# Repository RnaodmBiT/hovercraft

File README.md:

# MiniBot

This project will produce a PCB design that can be used for prototyping remote control vehicles. It is inspired by the University of Canterbury ECE Departments 'Wacky Racers' competition. The objective is to follow most of the rules of that competition however the entire design will fit on a single PCB and be as small as possible.

 ## Requirements
  - Support a number of external ESCs and Servos.
  - Be remote controlled. This might require a second USB dongle to be produced if Bluetooth or WiFi isn't used.
  - It should include an accelerometer, gyroscope, and magnetometer for any control systems.
  - Be programmable over SWD or USB.
  - Use as minimum number of parts.
  - Make use of an STM32 microcontroller.
  - Provide external PIO access for use in different projects.

 ## Connectivity
  - Radio
    - RN41
      - UART
      - LED connected to GPIO5 (Open Drain)
      - Connect GPIOs 3/4/6 to GND
      - Connect GPIO 7 to ground with solder bridge high

  - Accelerometer
    - LSM6DS3US
      - I2C

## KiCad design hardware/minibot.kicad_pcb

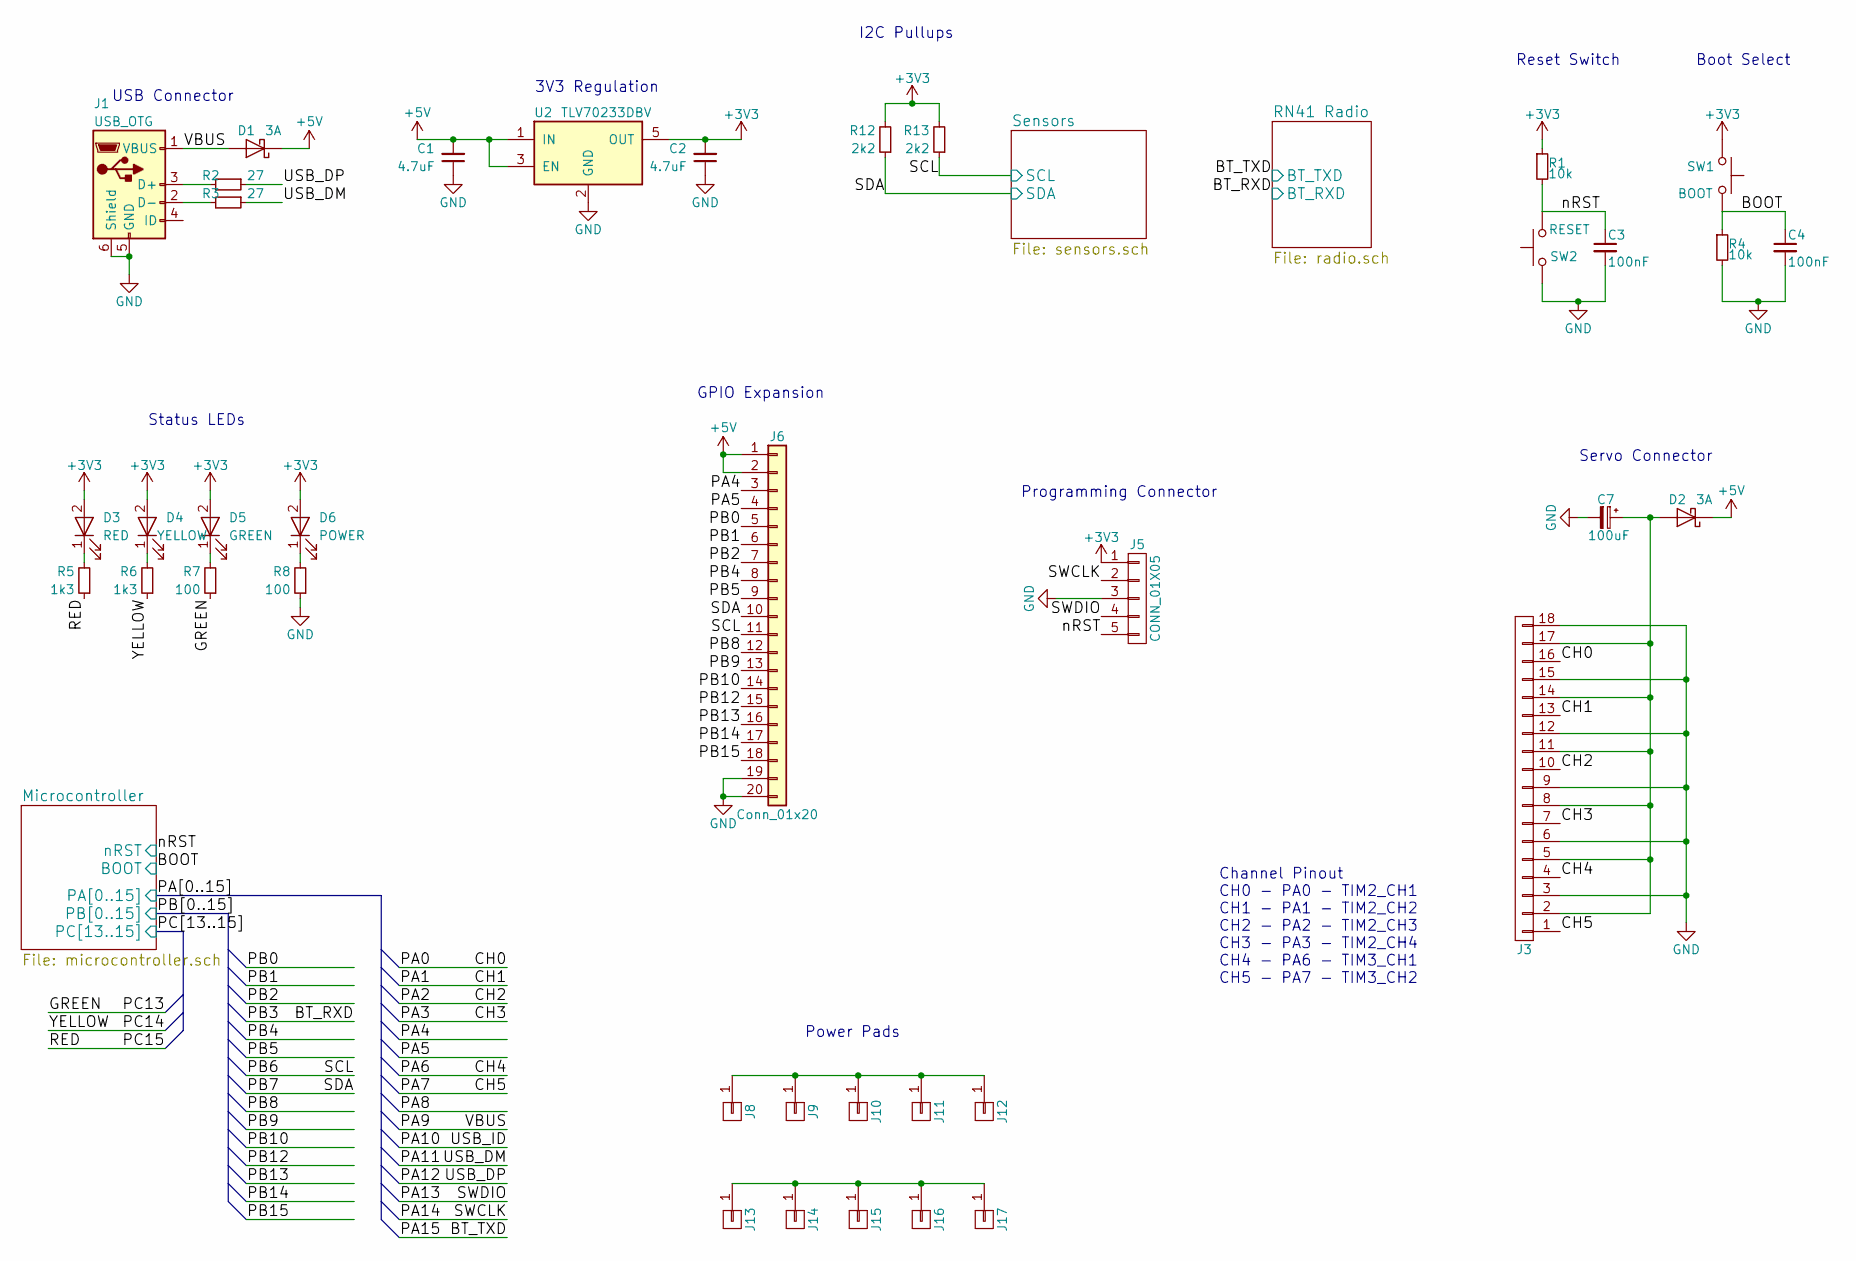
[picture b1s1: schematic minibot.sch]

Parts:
C1, C2: 4.7uF; C_0805
C3, C4: 100nF; C_0603
C7: 100uF; CP_Elec_6.3x5.3
D1, D2: 3A; D_SMA
D3: RED; LED_0603
D4: YELLOW; LED_0603
D5: GREEN; LED_0603
D6: POWER; LED_0603
J1: USB_OTG; USB_Micro-B
J3: CONN_01X18; Pin_Header_Angled_3x06_Pitch2.54mm
J5: CONN_01X05; Pin_Header_Straight_1x05_Pitch2.54mm
J6: Conn_01x20; IDC_Header_Straight_20pins
J8, J9, J10, J11, J12, J13, J14, J15, J16, J17: CONN_01X01; Pad
R1, R4: 10k; R_0603
R2, R3: 27; R_0603
R5, R6: 1k3; R_0603
R7, R8: 100; R_0603
R12, R13: 2k2; R_0603
SW1: BOOT; Panasonic_EVQPUK_EVQPUB
SW2: RESET; Panasonic_EVQPUK_EVQPUB
U2: TLV70233DBV; SOT-23-5

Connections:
+3V3: C2.2, D3.2 (A), D4.2 (A), D5.2 (A), D6.2 (A), J5.1, R1.1, R12.2, R13.2, SW1.1, U2.5 (OUT); also elsewhere on the board
+5V: C1.2, D1.1 (K), D2.1 (K), J6.1, J6.2, U2.1 (IN), U2.3 (EN)
/BOOT: C4.1, R4.1, SW1.2; also elsewhere on the board
/CH0: J3.16; also elsewhere on the board
/CH1: J3.13; also elsewhere on the board
/CH2: J3.10; also elsewhere on the board
/CH3: J3.7; also elsewhere on the board
/CH4: J3.4; also elsewhere on the board
/CH5: J3.1; also elsewhere on the board
/GREEN: R7.1; also elsewhere on the board
/PA4: J6.3; also elsewhere on the board
/PA5: J6.4; also elsewhere on the board
/PA9: D1.2 (A), J1.1 (VBUS); also elsewhere on the board
/PA11: R3.1; also elsewhere on the board
/PA12: R2.1; also elsewhere on the board
/PA13: J5.4; also elsewhere on the board
/PA14: J5.2; also elsewhere on the board
/PB0: J6.5; also elsewhere on the board
/PB1: J6.6; also elsewhere on the board
/PB2: J6.7; also elsewhere on the board
/PB4: J6.8; also elsewhere on the board
/PB5: J6.9; also elsewhere on the board
/PB6: J6.11, R13.1; also elsewhere on the board
/PB7: J6.10, R12.1; also elsewhere on the board
/PB8: J6.12; also elsewhere on the board
/PB9: J6.13; also elsewhere on the board
/PB10: J6.14; also elsewhere on the board
/PB12: J6.15; also elsewhere on the board
/PB13: J6.16; also elsewhere on the board
/PB14: J6.17; also elsewhere on the board
/PB15: J6.18; also elsewhere on the board
/PC14: R6.1; also elsewhere on the board
/PC15: R5.1; also elsewhere on the board
/nRST: C3.1, J5.5, R1.2, SW2.2; also elsewhere on the board
GND: C1.1, C2.1, C3.2, C4.2, C7.2, J1.5 (GND), J1.6 (Shield), J3.3, J3.6, J3.9, J3.12, J3.15, J3.18, J5.3, J6.19, J6.20, R4.2, R8.1, SW2.1, U2.2 (GND); also elsewhere on the board
unnamed: C7.1, D2.2 (A), J3.2, J3.5, J3.8, J3.11, J3.14, J3.17
unnamed: D3.1 (K), R5.2
unnamed: D4.1 (K), R6.2
unnamed: D5.1 (K), R7.2
unnamed: D6.1 (K), R8.2
unnamed: J1.2 (D-), R3.2
unnamed: J1.3 (D+), R2.2
unnamed: J8.1, J9.1, J10.1, J11.1, J12.1
unnamed: J13.1, J14.1, J15.1, J16.1, J17.1

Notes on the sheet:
Reset Switch
Boot Select
Servo Connector
USB Connector
3V3 Regulation
Status LEDs
Programming Connector
I2C Pullups
Channel Pinout CH0 - PA0 - TIM2_CH1 CH1 - PA1 - TIM2_CH2 CH2 - PA2 - TIM2_CH3 CH3 - PA3 - TIM2_CH4 CH4 - PA6 - TIM3_CH1 CH5 - PA7 - TIM3_CH2
GPIO Expansion
Power Pads

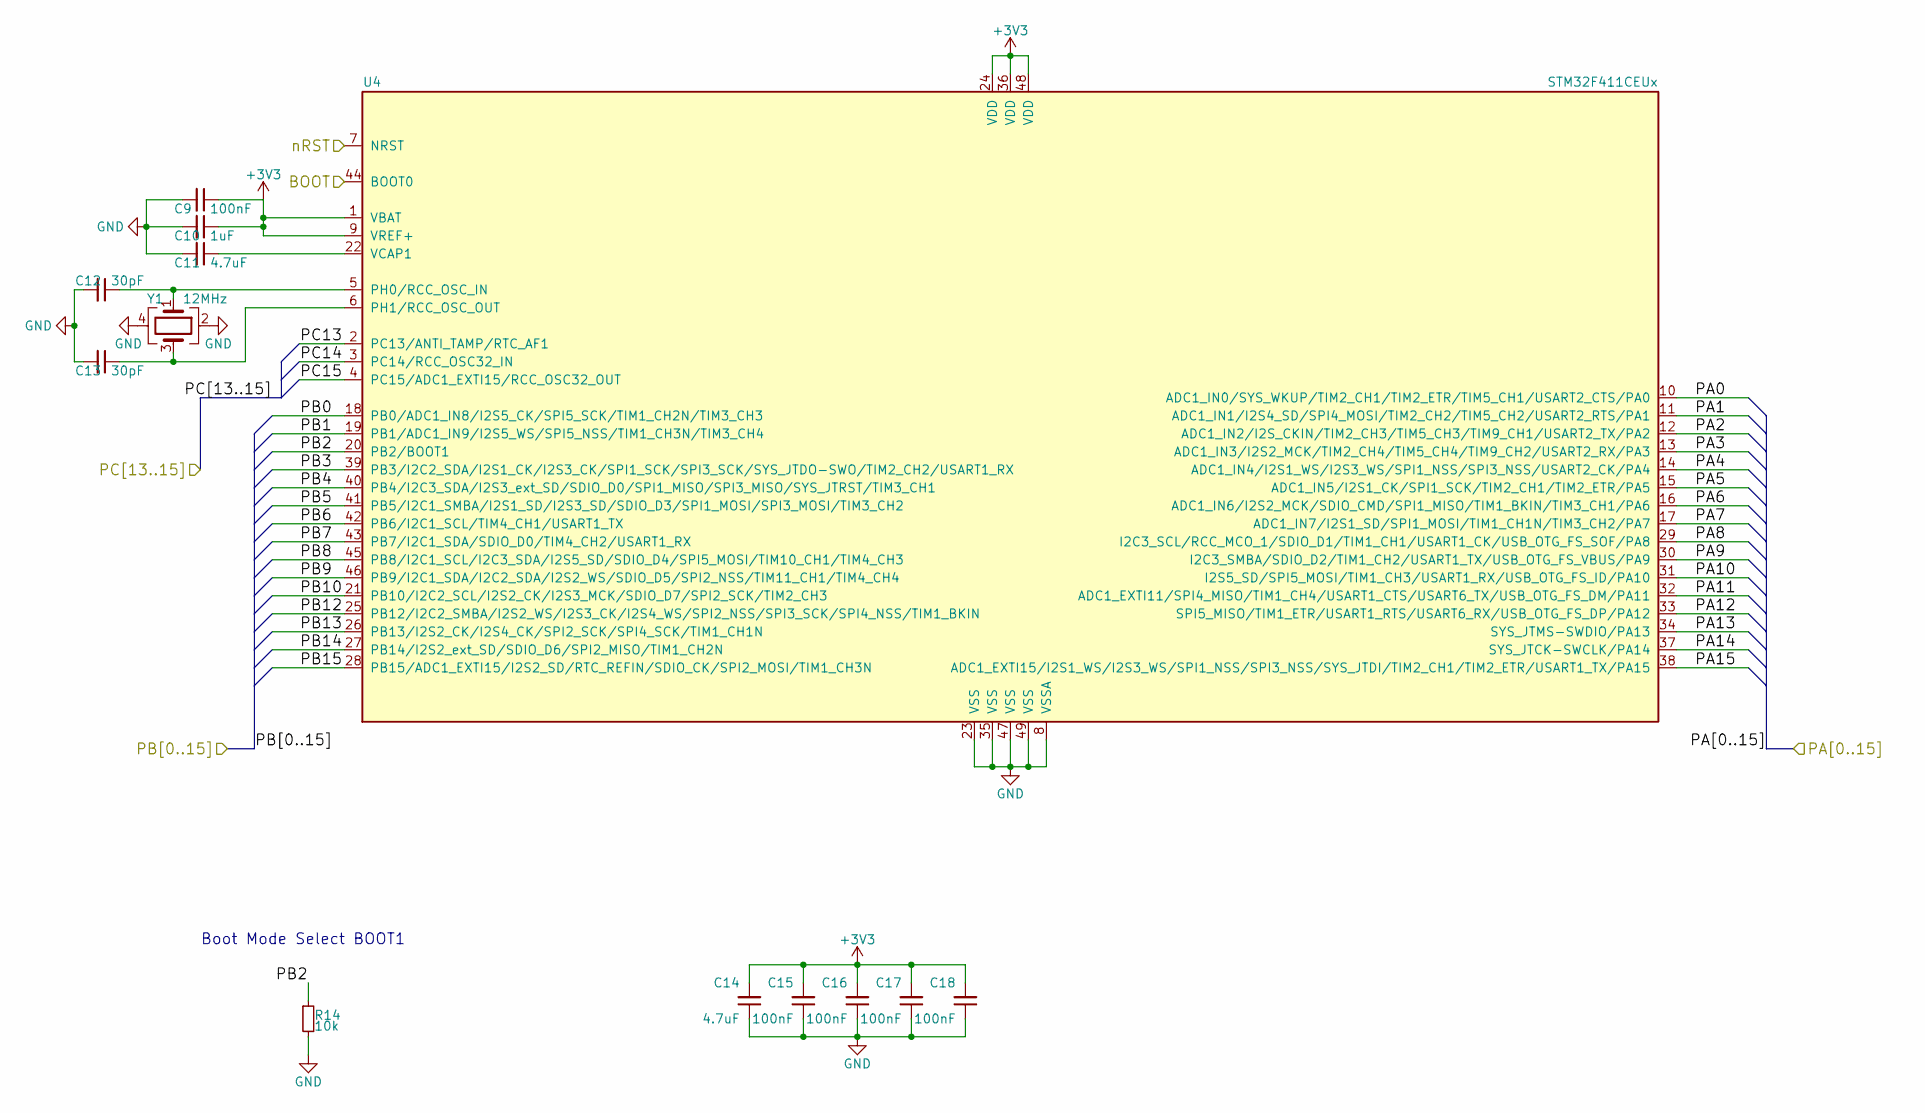
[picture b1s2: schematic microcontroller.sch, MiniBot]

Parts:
C9, C15, C16, C17, C18: 100nF; C_0603
C10: 1uF; C_0805
C11, C14: 4.7uF; C_0805
C12, C13: 30pF; C_0402
R14: 10k; R_0603
U4: STM32F411CEUx; TQFP-48_7x7mm_Pitch0.5mm
Y1: 12MHz; Crystal_SMD_3225-4pin_3.2x2.5mm

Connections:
+3V3: C9.1, C10.1, C14.2, C15.2, C16.2, C17.2, C18.2, U4.1 (VBAT), U4.9 (VREF+), U4.24 (VDD), U4.36 (VDD), U4.48 (VDD); also elsewhere on the board
/BOOT: U4.44 (BOOT0); also elsewhere on the board
/BT_RXD: U4.39 (PB3/I2C2_SDA/I2S1_CK/I2S3_CK/SPI1_SCK/S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); also elsewhere on the board
/BT_TXD: U4.38 (ADC1_EXTI15/I2S1_WS/I2S3_WS/SPI1_NSS/SP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); also elsewhere on the board
/CH0: U4.10 (ADC1_IN0/SYS_WKUP/TIM2_CH1/TIM2_ETR/TIM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); also elsewhere on the board
/CH1: U4.11 (ADC1_IN1/I2S4_SD/SPI4_MOSI/TIM2_CH2/TIM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); also elsewhere on the board
/CH2: U4.12 (ADC1_IN2/I2S_CKIN/TIM2_CH3/TIM5_CH3/TIM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); also elsewhere on the board
/CH3: U4.13 (ADC1_IN3/I2S2_MCK/TIM2_CH4/TIM5_CH4/TIM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); also elsewhere on the board
/CH4: U4.16 (ADC1_IN6/I2S2_MCK/SDIO_CMD/SPI1_MISO/TI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); also elsewhere on the board
/CH5: U4.17 (ADC1_IN7/I2S1_SD/SPI1_MOSI/TIM1_CH1N/TI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); also elsewhere on the board
/GREEN: U4.2 (PC13/ANTI_TAMP/RTC_AF1); also elsewhere on the board
/PA4: U4.14 (ADC1_IN4/I2S1_WS/I2S3_WS/SPI1_NSS/SPI3_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); also elsewhere on the board
/PA5: U4.15 (ADC1_IN5/I2S1_CK/SPI1_SCK/TIM2_CH1/TIM2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); also elsewhere on the board
/PA8: U4.29 (I2C3_SCL/RCC_MCO_1/SDIO_D1/TIM1_CH1/USA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)
/PA9: U4.30 (I2C3_SMBA/SDIO_D2/TIM1_CH2/USART1_TX/US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); also elsewhere on the board
/PA10: U4.31 (I2S5_SD/SPI5_MOSI/TIM1_CH3/USART1_RX/US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)
/PA11: U4.32 (ADC1_EXTI11/SPI4_MISO/TIM1_CH4/USART1_C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); also elsewhere on the board
/PA12: U4.33 (SPI5_MISO/TIM1_ETR/USART1_RTS/USART6_RX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); also elsewhere on the board
/PA13: U4.34 (SYS_JTMS-SWDIO/PA13); also elsewhere on the board
/PA14: U4.37 (SYS_JTCK-SWCLK/PA14); also elsewhere on the board
/PB0: U4.18 (PB0/ADC1_IN8/I2S5_CK/SPI5_SCK/TIM1_CH2N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); also elsewhere on the board
/PB1: U4.19 (PB1/ADC1_IN9/I2S5_WS/SPI5_NSS/TIM1_CH3N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); also elsewhere on the board
/PB2: R14.1, U4.20 (PB2/BOOT1); also elsewhere on the board
/PB4: U4.40 (PB4/I2C3_SDA/I2S3_ext_SD/SDIO_D0/SPI1_M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); also elsewhere on the board
/PB5: U4.41 (PB5/I2C1_SMBA/I2S1_SD/I2S3_SD/SDIO_D3/S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); also elsewhere on the board
/PB6: U4.42 (PB6/I2C1_SCL/TIM4_CH1/USART1_TX); also elsewhere on the board
/PB7: U4.43 (PB7/I2C1_SDA/SDIO_D0/TIM4_CH2/USART1_RX); also elsewhere on the board
/PB8: U4.45 (PB8/I2C1_SCL/I2C3_SDA/I2S5_SD/SDIO_D4/S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); also elsewhere on the board
/PB9: U4.46 (PB9/I2C1_SDA/I2C2_SDA/I2S2_WS/SDIO_D5/S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); also elsewhere on the board
/PB10: U4.21 (PB10/I2C2_SCL/I2S2_CK/I2S3_MCK/SDIO_D7/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); also elsewhere on the board
/PB12: U4.25 (PB12/I2C2_SMBA/I2S2_WS/I2S3_CK/I2S4_WS/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); also elsewhere on the board
/PB13: U4.26 (PB13/I2S2_CK/I2S4_CK/SPI2_SCK/SPI4_SCK/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); also elsewhere on the board
/PB14: U4.27 (PB14/I2S2_ext_SD/SDIO_D6/SPI2_MISO/TIM1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); also elsewhere on the board
/PB15: U4.28 (PB15/ADC1_EXTI15/I2S2_SD/RTC_REFIN/SDIO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); also elsewhere on the board
/PC14: U4.3 (PC14/RCC_OSC32_IN); also elsewhere on the board
/PC15: U4.4 (PC15/ADC1_EXTI15/RCC_OSC32_OUT); also elsewhere on the board
/nRST: U4.7 (NRST); also elsewhere on the board
GND: C9.2, C10.2, C11.2, C12.2, C13.2, C14.1, C15.1, C16.1, C17.1, C18.1, R14.2, U4.8 (VSSA), U4.23 (VSS), U4.35 (VSS), U4.47 (VSS), U4.49 (VSS), Y1.2, Y1.4; also elsewhere on the board
unnamed: C11.1, U4.22 (VCAP1)
unnamed: C12.1, U4.5 (PH0/RCC_OSC_IN), Y1.1
unnamed: C13.1, U4.6 (PH1/RCC_OSC_OUT), Y1.3

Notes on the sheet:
Boot Mode Select BOOT1

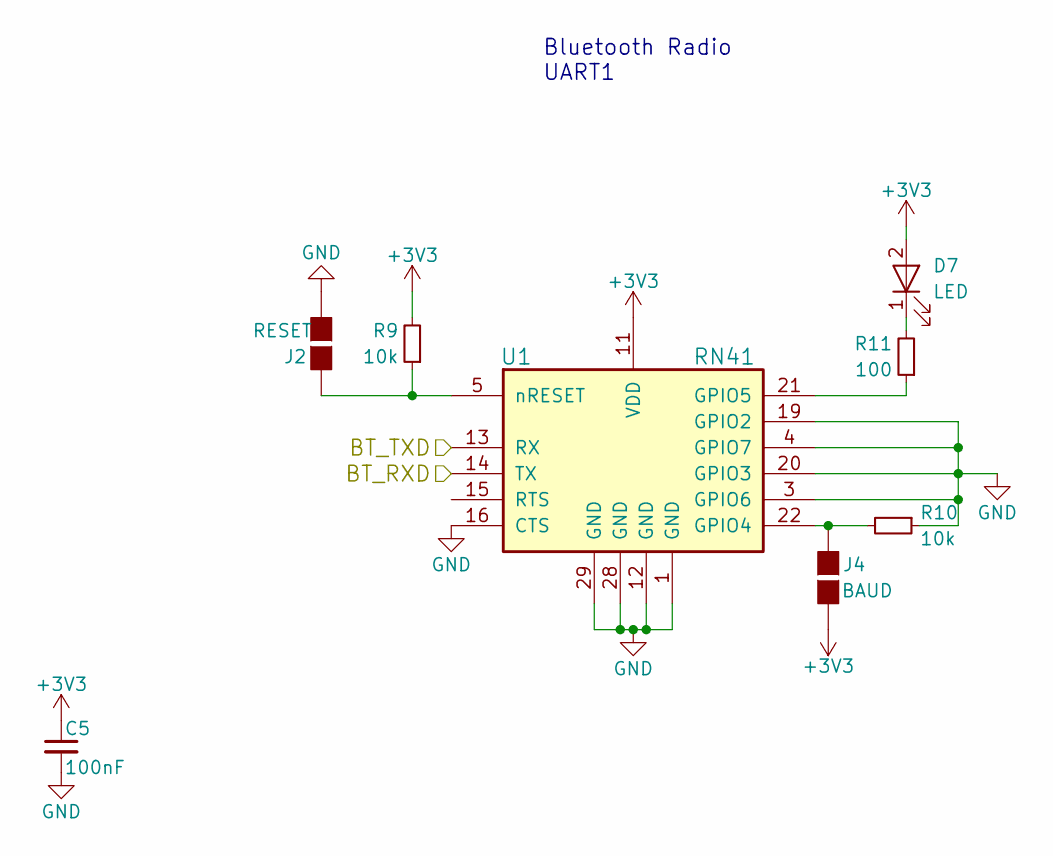
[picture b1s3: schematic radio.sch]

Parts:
C5: 100nF; C_0603
D7: LED; LED_0603
J2: RESET; GS2
J4: BAUD; GS2
R9, R10: 10k; R_0603
R11: 100; R_0603
U1: RN41

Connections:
+3V3: C5.1, D7.2 (A), J4.2 (G2), R9.2, U1.11 (VDD); also elsewhere on the board
/BT_RXD: U1.14 (TX); also elsewhere on the board
/BT_TXD: U1.13 (RX); also elsewhere on the board
GND: C5.2, J2.2 (G2), R10.1, U1.1 (GND), U1.3 (GPIO6), U1.4 (GPIO7), U1.12 (GND), U1.16 (CTS), U1.19 (GPIO2), U1.20 (GPIO3), U1.28 (GND), U1.29 (GND); also elsewhere on the board
unnamed: D7.1 (K), R11.2
unnamed: J2.1 (G1), R9.1, U1.5 (nRESET)
unnamed: J4.1 (G1), R10.2, U1.22 (GPIO4)
unnamed: R11.1, U1.21 (GPIO5)

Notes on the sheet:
Bluetooth Radio UART1

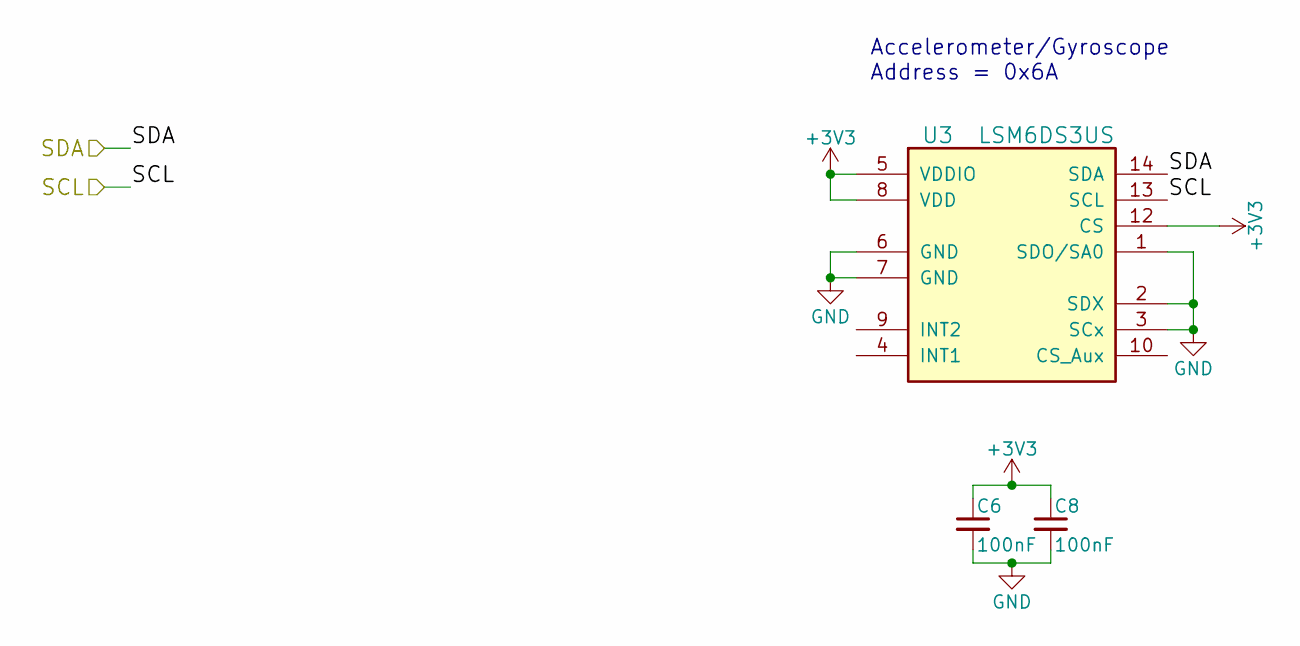
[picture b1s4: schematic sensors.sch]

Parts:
C6, C8: 100nF; C_0603
U3: LSM6DS3US

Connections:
+3V3: C6.1, C8.1, U3.5 (VDDIO), U3.8 (VDD), U3.12 (CS); also elsewhere on the board
/PB6: U3.13 (SCL); also elsewhere on the board
/PB7: U3.14 (SDA); also elsewhere on the board
GND: C6.2, C8.2, U3.1 (SDO/SA0), U3.2 (SDX), U3.3 (SCx), U3.6 (GND), U3.7 (GND); also elsewhere on the board

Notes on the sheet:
Accelerometer/Gyroscope Address = 0x6A

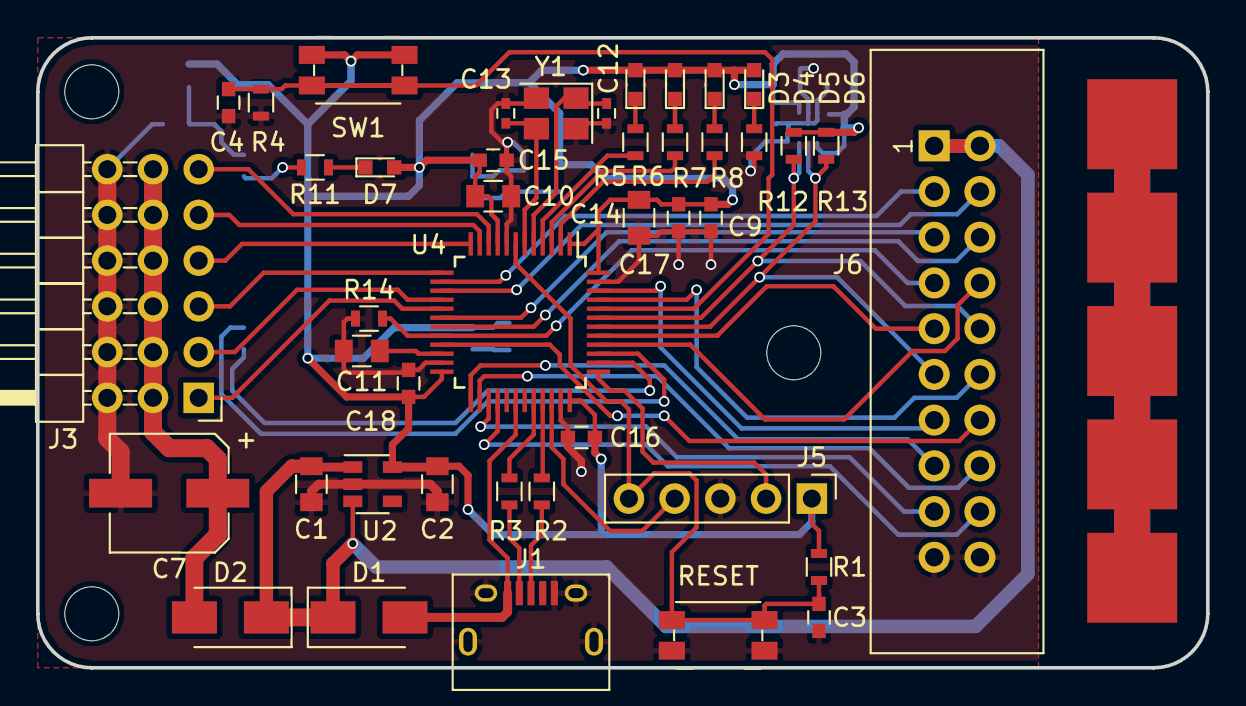
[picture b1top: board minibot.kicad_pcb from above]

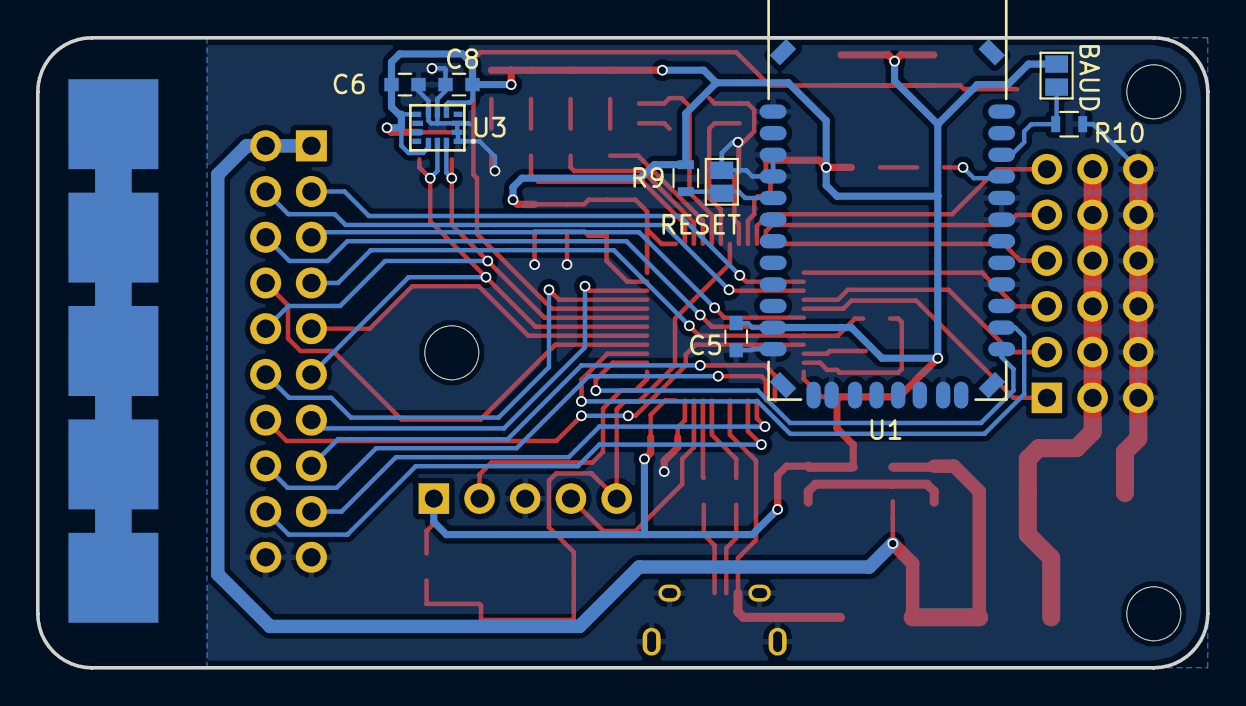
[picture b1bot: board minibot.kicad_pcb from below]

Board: 2 copper layers, 65.0 x 35.0 mm, 62 parts (14 on the bottom side), 53 nets.

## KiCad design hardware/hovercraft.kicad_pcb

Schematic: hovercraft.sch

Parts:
C1, C2, C5, C6, C7, C8, C9: 1uF; C_0603
C3, C4: 30pF; C_0603
D1, D2: D_Schottky_Small; D_SMA
D3: POWER; LED_0603
D4: GREEN; LED_0603
D5: YELLOW; LED_0603
D6: RED; LED_0603
J1: USB_OTG; USB_Micro-B
J2, J3, J4, J5, J6, J7: CONN_01X03; Pin_Header_Angled_1x03_Pitch2.54mm
J8, J9, J10, J11, J12: CONN_01X02; XT60
R1, R4: 10k; R_0603
R2, R3: 22; R_0603
R5, R6: 1K8; R_0603
R7, R8: 3K; R_0603
SW1: RESET; Panasonic_EVQPUJ_EVQPUA
SW2: BOOT; Panasonic_EVQPUJ_EVQPUA
U1: HC-12
U2: ATMEGA32U2-AU; QFN-32-1EP_5x5mm_Pitch0.5mm
Y1: Crystal_GND24; Crystal_SMD_5032-4pin_5.0x3.2mm

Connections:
/CH0: J2.1, U2.14 ((~SS~/PCINT0)PB0)
/CH1: J3.1, U2.15 ((SCLK/PCINT1)PB1)
/CH2: J4.1, U2.16 ((PDI/MOSI/PCINT2)PB2)
/CH3: J5.1, U2.17 ((PD0/MISO/PCINT3)PB3)
/CH4: J6.1, U2.18 ((T1/PCINT4)PB4)
/CH5: J7.1, U2.19 ((PCINT5)PB5)
/MCU_RXD: U1.4, U2.8 ((RXD1/AIN1/INT2)PD2)
/MCU_TXD: U1.3, U2.9 ((TXD1/INT3)PD3)
/USB_N: J1.2 (D-), R3.2
/USB_P: J1.3 (D+), R2.2
/VBUS: D1.2, J1.1 (VBUS), U2.31 (UVCC)
GND: C1.2, C2.2, C3.1, C4.1, C5.2, C6.1, C7.2, C8.2, C9.2, J1.5 (GND), J1.6 (Shield), J2.3, J3.3, J4.3, J5.3, J6.3, J7.3, R5.2, SW1.1, SW2.1, U1.2, U1.7, U1.8, U2.3 (GND), U2.28 (UGND), U2.33, Y1.2, Y1.4
unnamed: C1.1, C2.1, C5.1, C7.1, C8.1, C9.1, D2.2, J2.2, J3.2, J4.2, J5.2, J6.2, J7.2
unnamed: C3.2, U2.1 (XTAL1), Y1.1
unnamed: C4.2, U2.2 (PC0(XTAL2)), Y1.3
unnamed: C6.2, U2.27 (UCAP)
unnamed: D3.1 (K), R5.1
unnamed: D4.1 (K), R6.1
unnamed: D5.1 (K), R7.1
unnamed: D6.1 (K), R8.1
unnamed: J8.1, J9.1, J10.1, J11.1, J12.1
unnamed: J8.2, J9.2, J10.2, J11.2, J12.2
unnamed: R1.2, SW1.2, U2.24 (PC1(~RESET~/dW))
unnamed: R2.1, U2.29 (D+)
unnamed: R3.1, U2.30 (D-)
unnamed: R4.1, SW2.2, U2.13 ((~CTS~/~HWB~/AIN6/T0/INT7)PD7)
unnamed: R6.2, U2.12 ((~RTS~/AIN5/INT6)PD6)
unnamed: R7.2, U2.11 ((XCK/AIN4/PCINT12)PD5)
unnamed: R8.2, U2.10 ((INT5/AIN3)PD4)
VCC: D1.1, D2.1, D3.2 (A), D4.2 (A), D5.2 (A), D6.2 (A), R1.1, R4.2, U1.1, U2.4 (VCC), U2.32 (AVCC)

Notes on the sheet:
18pF Load Capacitance
3V2

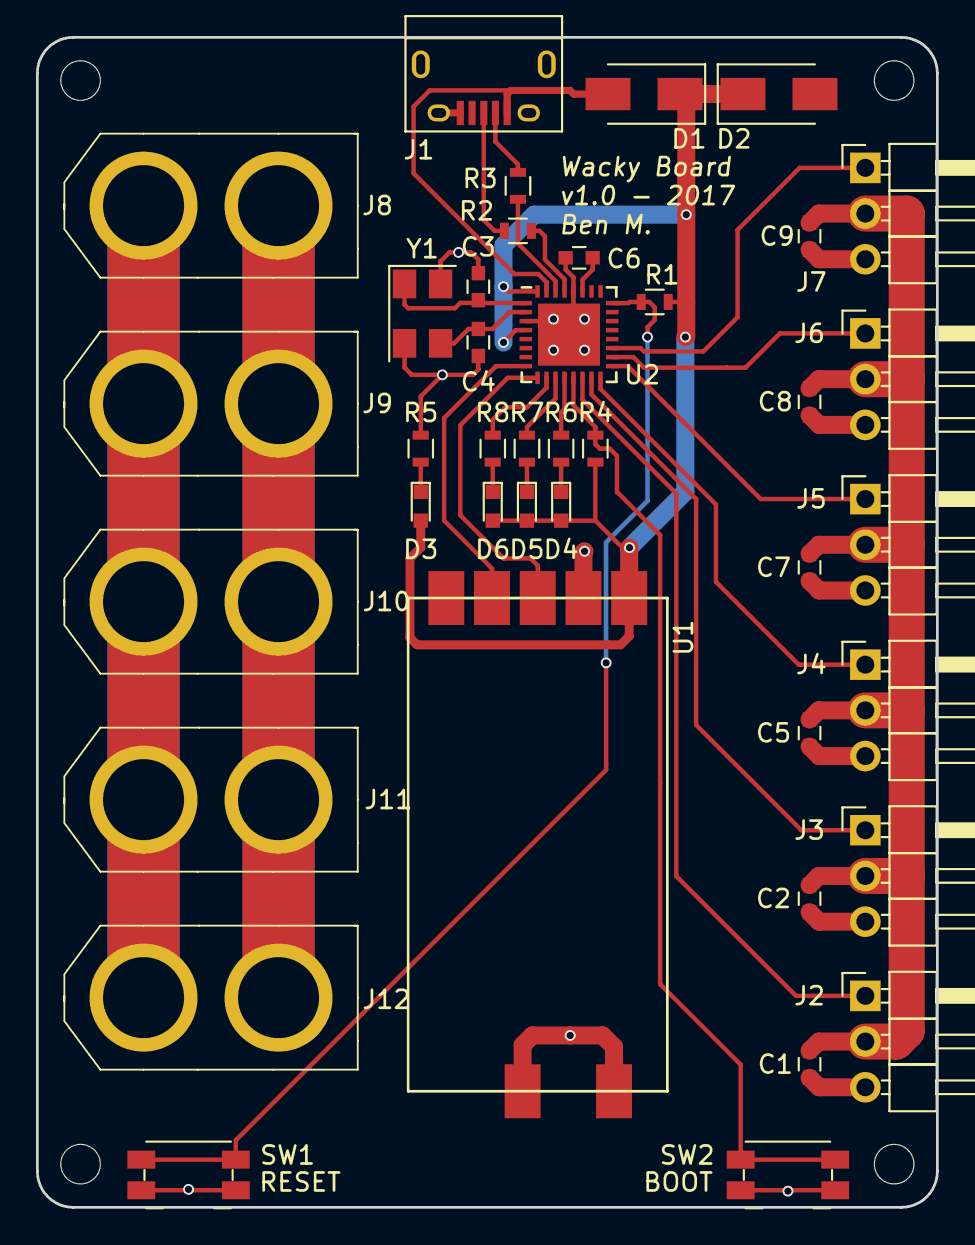
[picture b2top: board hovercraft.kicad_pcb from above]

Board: 2 copper layers, 50.0 x 65.0 mm, 40 parts (0 on the bottom side), 30 nets.

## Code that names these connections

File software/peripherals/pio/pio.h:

#ifndef PIO_H
#define PIO_H

#include <stdint.h>
#include <stdbool.h>

typedef struct {
    uint8_t port;
    uint8_t pin;
    uint16_t mask;
} __attribute__((packed)) pio_t;


typedef enum { PIO_A, PIO_B, PIO_C } pio_port_t;
typedef enum { PIO_INPUT, PIO_OUTPUT } pio_mode_t;

/* enable clock for the given PIO port */
void pio_enable_port(pio_port_t port);

/* set pin mode as input or output */
void pio_set_mode(pio_t pin, pio_mode_t mode);

/* set the pin output state */
void pio_set_output(pio_t pin, bool high);


/* Define all of the usable PIO pins */
#define MAKE_PIO(PORT, PIN) ((pio_t){ .port=(PORT), .pin=(PIN), .mask=1 << (PIN) })

#define PA0     MAKE_PIO(0, 0)
#define PA1     MAKE_PIO(0, 1)
#define PA2     MAKE_PIO(0, 2)
#define PA3     MAKE_PIO(0, 3)
#define PA4     MAKE_PIO(0, 4)
#define PA5     MAKE_PIO(0, 5)
#define PA6     MAKE_PIO(0, 6)
#define PA7     MAKE_PIO(0, 7)
#define PA8     MAKE_PIO(0, 8)
#define PA9     MAKE_PIO(0, 9)
#define PA10    MAKE_PIO(0, 10)
#define PA11    MAKE_PIO(0, 11)
#define PA12    MAKE_PIO(0, 12)
#define PA13    MAKE_PIO(0, 13)
#define PA14    MAKE_PIO(0, 14)
#define PA15    MAKE_PIO(0, 15)


#define PB0     MAKE_PIO(1, 0)
#define PB1     MAKE_PIO(1, 1)
#define PB2     MAKE_PIO(1, 2)
#define PB3     MAKE_PIO(1, 3)
#define PB4     MAKE_PIO(1, 4)
#define PB5     MAKE_PIO(1, 5)
#define PB6     MAKE_PIO(1, 6)
#define PB7     MAKE_PIO(1, 7)
#define PB8     MAKE_PIO(1, 8)
#define PB9     MAKE_PIO(1, 9)
#define PB10    MAKE_PIO(1, 10)
#define PB11    MAKE_PIO(1, 11)
#define PB12    MAKE_PIO(1, 12)
#define PB13    MAKE_PIO(1, 13)
#define PB14    MAKE_PIO(1, 14)
#define PB15    MAKE_PIO(1, 15)


#define PC13    MAKE_PIO(2, 13)
#define PC14    MAKE_PIO(2, 14)
#define PC15    MAKE_PIO(2, 15)

#endif

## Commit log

2017-06-09 Add initial PCB design with the ATMEGA32U2 and USB power
2017-06-09 Finish the basic layout of the micro. Next the power needs to be sorted and how the micro will talk to the motors
2017-06-11 Filled out the schematic with servo and power connectors and populated these on the PCB
2017-06-11 Add the HC-12 serial radio module to the component library
2017-06-11 Add the HC-12 foot print and repopulate the board to fit it in.
2017-06-11 Added the board dimensions to the layout
2017-06-11 Increased some trace thicknesses around the servo connections to reduce thermal buildup
2017-06-12 Separated some traces to try reduce crosstalk. Also added a name and version number to the board
2017-06-12 Extend the board size to a more natural number and add mounting holes
2017-06-13 Moved the servo PWM signals to different pins to free up the SPI for a gyroscope/accelerometer/magnetometer
2017-06-13 Tidied up the file structure
2017-06-13 Plot a PDF of the schematic
2017-06-13 Add decoupling to the micro, radio, and USB power
2017-06-13 Update the schematic PDF
2017-06-14 Upgrade the specifications and wipe the previous attempt as we will need to start again.
2017-06-14 Added a simple STM32 schematic. This includes power, clock, and busses for the GPIO
2017-06-14 Add the RFM69 datasheet as this could be a potential RF module for the project
2017-06-15 Moved the microcontroller to another sheet and setup the boot and reset switches
2017-06-15 Add the RN41 radio and a header for the servos
2017-06-15 Add a USB connector and 3.3V regulation
2017-06-15 Broke out the A and B PIO ports. Added status LEDs
2017-06-15 Fix the PORT A numbering. Add the ST Link JTAG connector
2017-06-16 Change the JTAG connector to an SWD connector. Also start connecting the MCU pins in a clear and visible manner
2017-06-16 Plotted the schematic
2017-06-16 Map the servo channels. Wire up the BT USART. Add an IMU and an I2C bus. Update the schematic PDF.
2017-06-16 Add missing decoupling capacitor to the RN41
2017-06-16 Map all of the inputs except for the debugging LEDs. Still need to work out how to deal with the camera.
2017-06-18 Add the camera and finish off the schematic.
2017-06-18 Fix the servo channels to ensure they use different PWM outputs. This required removing the flow control from the RN41 so CTS was tied to ground.
2017-06-18 Add missing camera decoupling. Annotate all parts.
2017-06-18 Associate the simple parts with footprints. Some custom footprints will need to be designed.
2017-06-19 Add in some logic level translation for the camera signals. Update the annotations and plot the PDF
2017-06-19 Plot the PDF in colour
2017-06-23 Remove the camera from the schematic as it's no longer a reasonable goal
2017-06-23 Update the README to reflect some of the project changes.
2017-06-23 Start adjusting the signals now that the camera isn't in the way
2017-06-23 Start laying out the components for the PCB
2017-06-26 Update the PDF
2017-06-26 Modify the schematic and PCB. At this stage the pinout should be considered and very careful selection of which peripheral goes where needs to be done.
2017-06-27 Redo the pinout. Plot the PDF. Layout the rest of the board.
2017-06-28 Tweak the layout a little bit. Add mounting holes and some pads to solder the power leads onto.
2017-06-28 Plot the latest schematic
2017-06-28 Move a trace to reduce crosstalk.
2017-06-29 Fix the USB overlapping with the RN41
2017-08-28 Move the radio, and the sensors to new schematic sheets.
2017-08-30 Layed board out for the third time. Doesn't include power traces yet.
2017-08-31 Finish routing the board again
2017-09-21 Add the gerber files
2017-09-22 Program the STM32F410CB
2017-09-22 Tidy up the build chain
2017-09-23 Move the pio code into the peripherals tree and automate the makefile for it
2017-09-23 Moved the initialised constants into flash memory for now. This needs to be fixed by doing a copy into SRAM to speed things up.
2017-09-23 Move the vector table and reset_handler into a sys moule. Use this to also setup the external crystal properly. Add a couple of vauge timing functions
2017-09-24 Blinky1 works. Don't touch it ever again.
2017-09-25 Add UART to the software. The minibot can now send 'hello world' over BT. Add the two programming manuals to the documents. Also fix the system clock
2017-09-27 Add uart echo program. Start building python interface. Add GDB and OpenOCD support with the STLinkV2
2017-09-28 Started moving the code base into C++. The Pio class is wonderful. Thought should be taken as to how sys and uart will look. The LEDs also flash REALLY fast now, this needs to be debugged
2017-09-29 Fix the linker script to include static data properly. Tweak the build script wrt peripherals. Test rudimentary SysTick code
2017-09-29 Get the clock running properly at 100 MHz and fix the delay functions.
2017-09-29 Updated the UART apps to the new C++ style. Fix the clocks for the UART, everything is awesome now. It just needs to be classed up
2017-09-30 Updated sys to C++ify it all. Tidy up blink1 to match.
2017-09-30 Update the uart driver to C++. Update uart1 to match
2017-09-30 Update uart_echo to c++ code
2017-09-30 Add actual MCU datasheet
2017-10-01 Add a new program and a python app intended to determine the max data rate of the RN41
2017-11-01 Add an IGBT driver program for the Groundwater project
2017-12-13 Add software PWM support.
2017-12-13 Added a helper function for dealing with servos
2017-12-13 Add a mini_tank program for the minibot and a python controller for it.
2017-12-15 Slow down the mini tank controller program and flush the bluetooth buffers for a faster connection
2017-12-15 Update git ignore for python cache
2017-12-15 Make the tank drive
2017-12-17 Move to a proper x/y control input with a timeout value
